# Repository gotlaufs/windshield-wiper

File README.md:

# windshield-wiper

Small device to control a Winshield Wiper Motor.

### Features
3 speed modes:
 - Slow
 - Fast
 - Interval (with selectable delay)

### Development
Uses MSP430G2553 MCU from TI.
Built using CCS and GCC compiler.

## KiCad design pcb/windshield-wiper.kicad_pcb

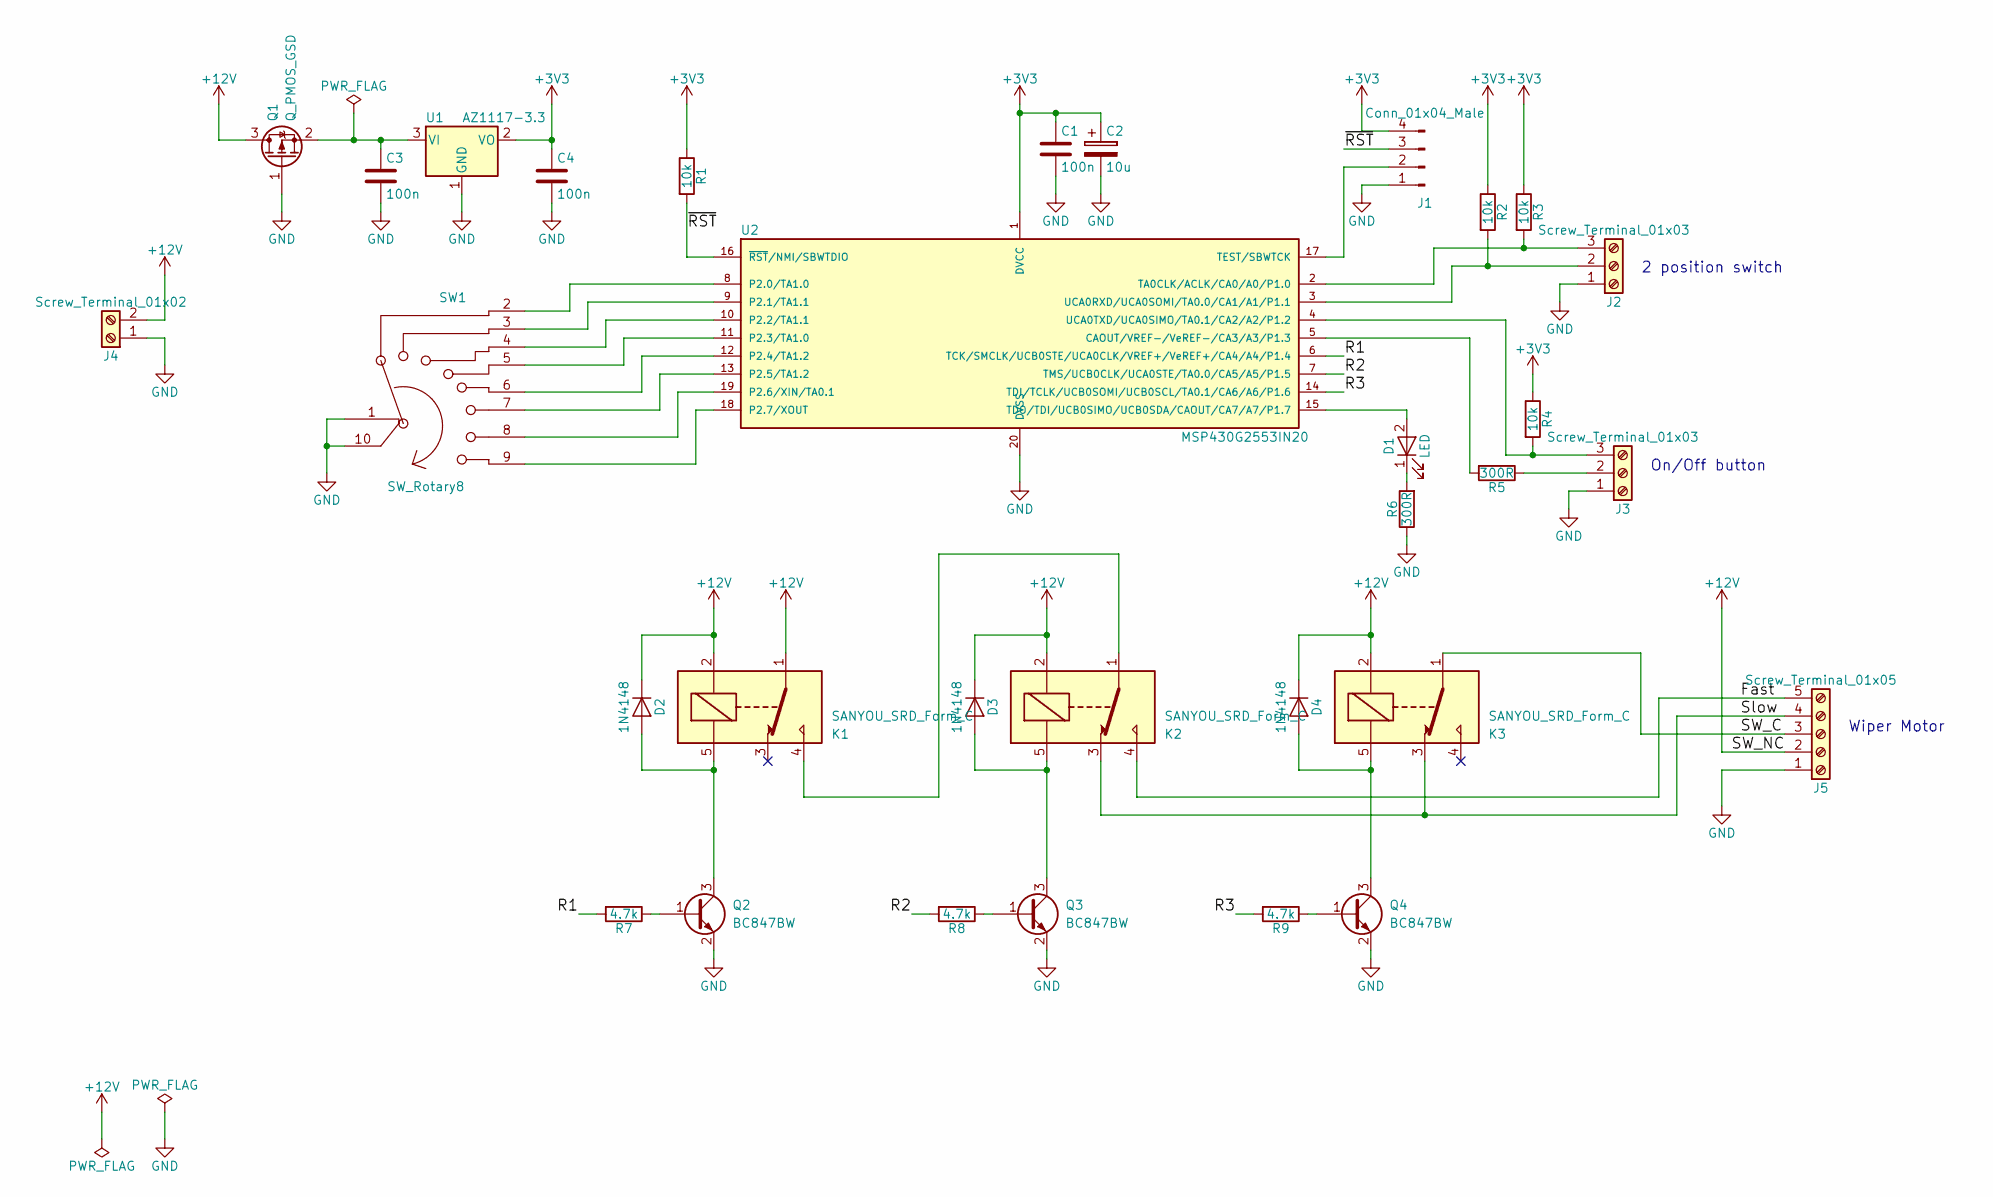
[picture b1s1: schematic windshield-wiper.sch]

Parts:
C1, C3, C4: 100n; C_0805_HandSoldering
C2: 10u; CP_Elec_6.3x5.3
D1: LED; LED_0805_HandSoldering
D2, D3, D4: 1N4148; D_SOD-123F
J1: Conn_01x04_Male; Pin_Header_Straight_1x04_Pitch2.54mm
J2, J3: Screw_Terminal_01x03; TerminalBlock_Phoenix_MPT-2.54mm_3pol
J4: Screw_Terminal_01x02; TerminalBlock_Phoenix_MPT-2.54mm_2pol
J5: Screw_Terminal_01x05; TerminalBlock_Phoenix_MPT-2.54mm_5pol
K1, K2, K3: SANYOU_SRD_Form_C; Relay_SPDT_SANYOU_SRD_Series_Form_C
Q1: Q_PMOS_GSD; SOT-23_Handsoldering
Q2, Q3, Q4: BC847BW; SOT-323_SC-70_Handsoldering
R1, R2, R3, R4: 10k; R_0805_HandSoldering
R5, R6: 300R; R_0805_HandSoldering
R7, R8, R9: 4.7k; R_0805_HandSoldering
SW1: SW_Rotary8; ROT_SW_8
U1: AZ1117-3.3; SOT-223-3_TabPin2
U2: MSP430G2553IN20; DIP-20_W7.62mm_LongPads

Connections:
+3V3: C1.1, C2.1, C4.1, J1.4, R1.1, R2.1, R3.1, R4.1, U1.2 (VO), U2.1 (DVCC)
+12V: D2.1 (K), D3.1 (K), D4.1 (K), J4.2, J5.2, K1.1, K1.2, K2.2, K3.2, Q1.3 (D)
/Fast: J5.5, K2.4
/R1: R7.2, U2.6 (TCK/SMCLK/UCB0STE/UCA0CLK/VREF+/VeREF+/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)
/R2: R8.2, U2.7 (TMS/UCB0CLK/UCA0STE/TA0.0/CA5/A5/P1.5)
/R3: R9.2, U2.14 (TDI/TCLK/UCB0SOMI/UCB0SCL/TA0.1/CA6/A6/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)
/SW_C: J5.3, K3.1
/Slow: J5.4, K2.3, K3.3
/~RST: J1.3, R1.2, U2.16 (~RST~/NMI/SBWTDIO)
GND: C1.2, C2.2, C3.2, C4.2, J1.1, J2.1, J3.1, J4.1, J5.1, Q1.1 (G), Q2.2 (E), Q3.2 (E), Q4.2 (E), R6.1, SW1.1, SW1.10, U1.1 (GND), U2.20 (DVSS)
unnamed: C3.1, Q1.2 (S), U1.3 (VI)
unnamed: D1.1 (K), R6.2
unnamed: D1.2 (A), U2.15 (TDO/TDI/UCB0SIMO/UCB0SDA/CAOUT/CA7/A7/P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)
unnamed: D2.2 (A), K1.5, Q2.3 (C)
unnamed: D3.2 (A), K2.5, Q3.3 (C)
unnamed: D4.2 (A), K3.5, Q4.3 (C)
unnamed: J1.2, U2.17 (TEST/SBWTCK)
unnamed: J2.2, R2.2, U2.3 (UCA0RXD/UCA0SOMI/TA0.0/CA1/A1/P1.1)
unnamed: J2.3, R3.2, U2.2 (TA0CLK/ACLK/CA0/A0/P1.0)
unnamed: J3.2, R5.1
unnamed: J3.3, R4.2, U2.4 (UCA0TXD/UCA0SIMO/TA0.1/CA2/A2/P1.2)
unnamed: K1.4, K2.1
unnamed: Q2.1 (B), R7.1
unnamed: Q3.1 (B), R8.1
unnamed: Q4.1 (B), R9.1
unnamed: R5.2, U2.5 (CAOUT/VREF-/VeREF-/CA3/A3/P1.3)
unnamed: SW1.2, U2.8 (P2.0/TA1.0)
unnamed: SW1.3, U2.9 (P2.1/TA1.1)
unnamed: SW1.4, U2.10 (P2.2/TA1.1)
unnamed: SW1.5, U2.11 (P2.3/TA1.0)
unnamed: SW1.6, U2.12 (P2.4/TA1.2)
unnamed: SW1.7, U2.13 (P2.5/TA1.2)
unnamed: SW1.8, U2.19 (P2.6/XIN/TA0.1)
unnamed: SW1.9, U2.18 (P2.7/XOUT)

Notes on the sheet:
2 position switch
On/Off button
Wiper Motor

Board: 2 copper layers, 32 parts (0 on the bottom side), 34 nets, no tracks yet.

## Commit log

2018-02-19 Initial CCS structure
2018-02-21 Add first code version
2018-02-22 Bugfixes
2018-03-01 Morestupid bugfixes
2018-03-01 Add some pics
2018-03-01 Update Readme again
2018-03-05 Start designing a PCB
2018-04-09 KiCad files
